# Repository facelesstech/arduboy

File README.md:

# arduboy
arduboy with flashcart

Blog post - https://facelesstech.wordpress.com/2019/10/12/arduboy-with-removable-flash-cart/
Youtube - https://youtu.be/qZQMl9mM28Q

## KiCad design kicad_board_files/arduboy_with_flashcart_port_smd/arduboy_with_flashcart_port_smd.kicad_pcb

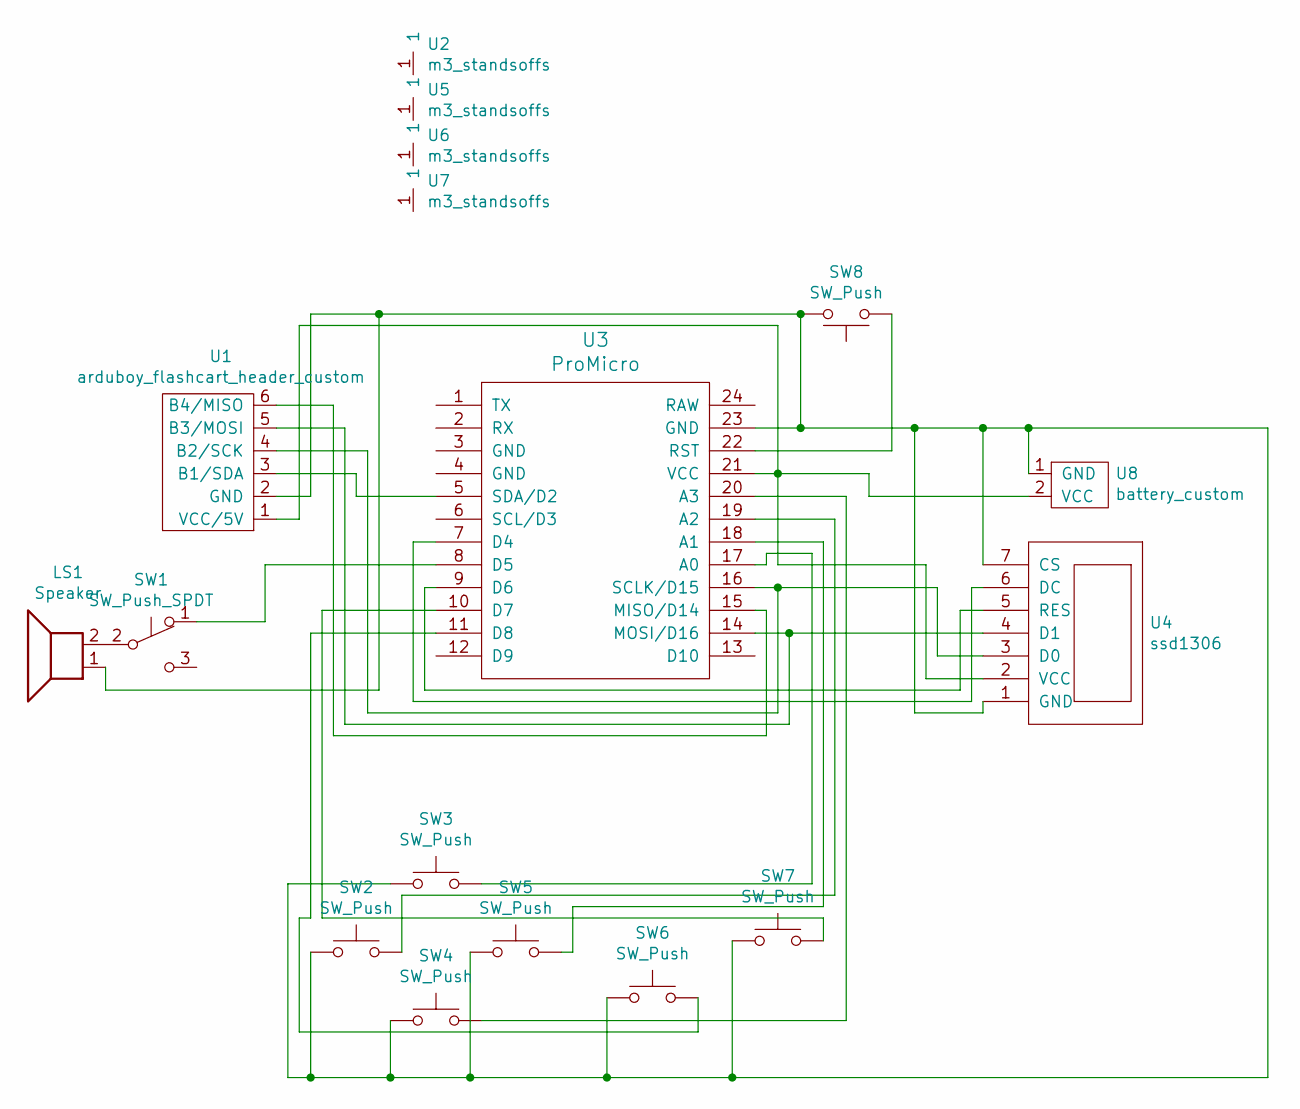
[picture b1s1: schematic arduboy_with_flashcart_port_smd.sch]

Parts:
LS1: Speaker; piezo_smd
SW1: SW_Push_SPDT; tiny_smd_slide_switch_custom
SW2, SW3, SW4, SW5, SW6, SW7: SW_Push; smd_soft_custom
SW8: SW_Push; SMD_2pin_button_custom
U1: arduboy_flashcart_header_custom; arduboy_flashcart_port_flashcart_outline
U2, U5, U6, U7: m3_standsoffs; m3_hole_custom
U3: ProMicro; ProMicro_smd_pads
U4: ssd1306; SSD1306_oled_screen
U8: battery_custom; battery_connector_custom

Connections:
unnamed: LS1.1, SW2.1, SW3.1, SW4.1, SW5.1, SW6.1, SW7.1, SW8.2, U1.2 (GND), U3.23 (GND), U4.1 (GND), U4.7 (CS), U8.1 (GND)
unnamed: LS1.2, SW1.2 (B)
unnamed: SW1.1 (A), U3.8 (D5)
unnamed: SW2.2, U3.19 (A2)
unnamed: SW3.2, U3.17 (A0)
unnamed: SW4.2, U3.20 (A3)
unnamed: SW5.2, U3.18 (A1)
unnamed: SW6.2, U3.11 (D8)
unnamed: SW7.2, U3.10 (D7)
unnamed: SW8.1, U3.22 (RST)
unnamed: U1.1 (VCC/5V), U3.21 (VCC), U4.2 (VCC), U8.2 (VCC)
unnamed: U1.3 (B1/SDA), U3.5 (SDA/D2)
unnamed: U1.4 (B2/SCK), U3.16 (SCLK/D15), U4.3 (D0)
unnamed: U1.5 (B3/MOSI), U3.14 (MOSI/D16), U4.4 (D1)
unnamed: U1.6 (B4/MISO), U3.15 (MISO/D14)
unnamed: U3.7 (D4), U4.6 (DC)
unnamed: U3.9 (D6), U4.5 (RES)

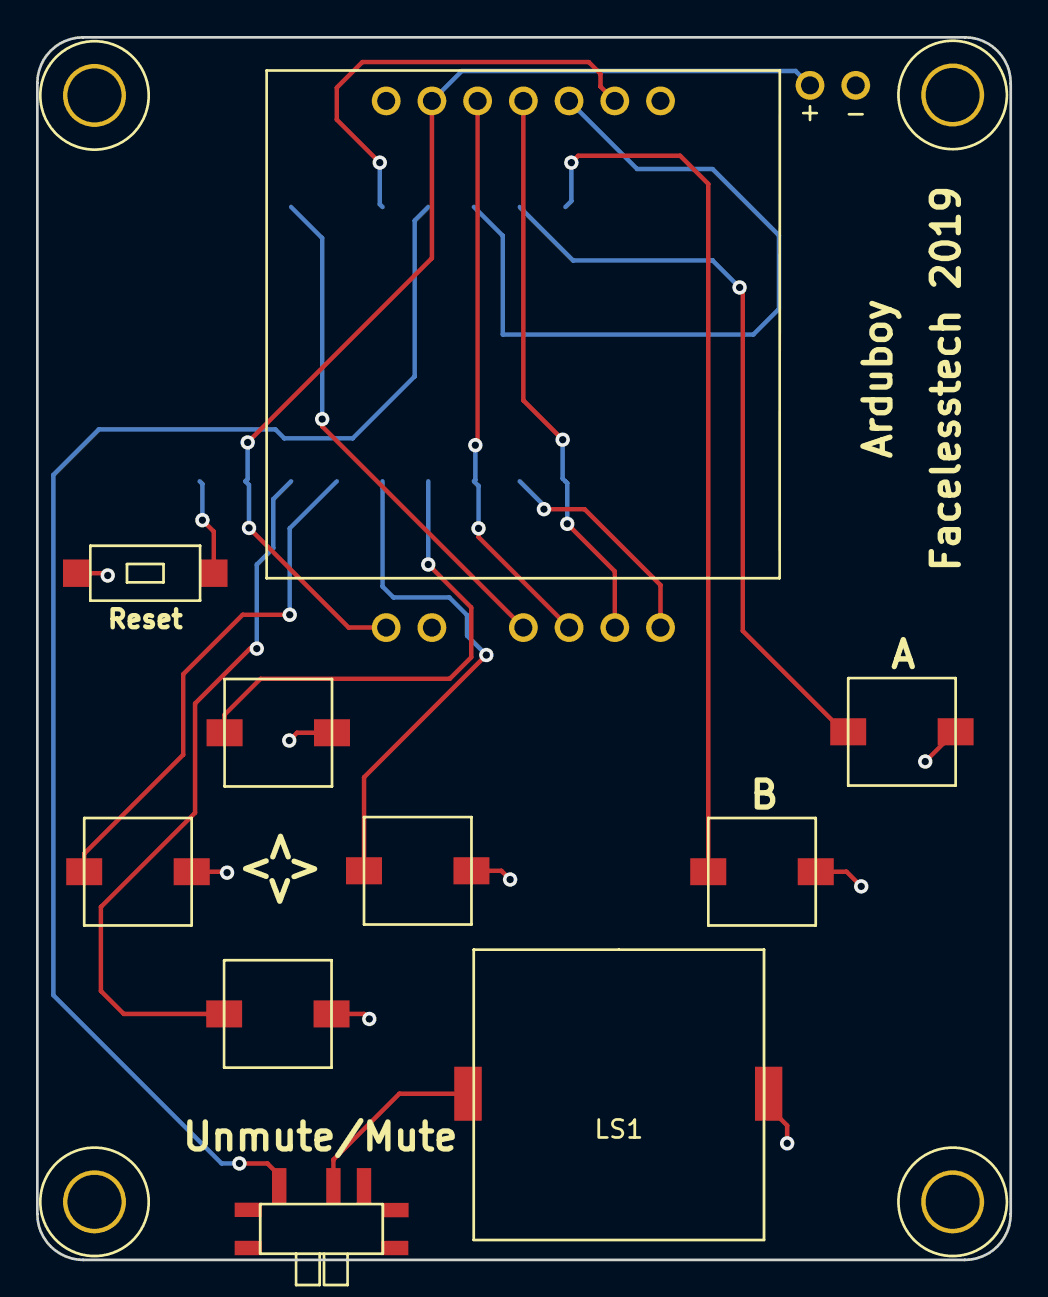
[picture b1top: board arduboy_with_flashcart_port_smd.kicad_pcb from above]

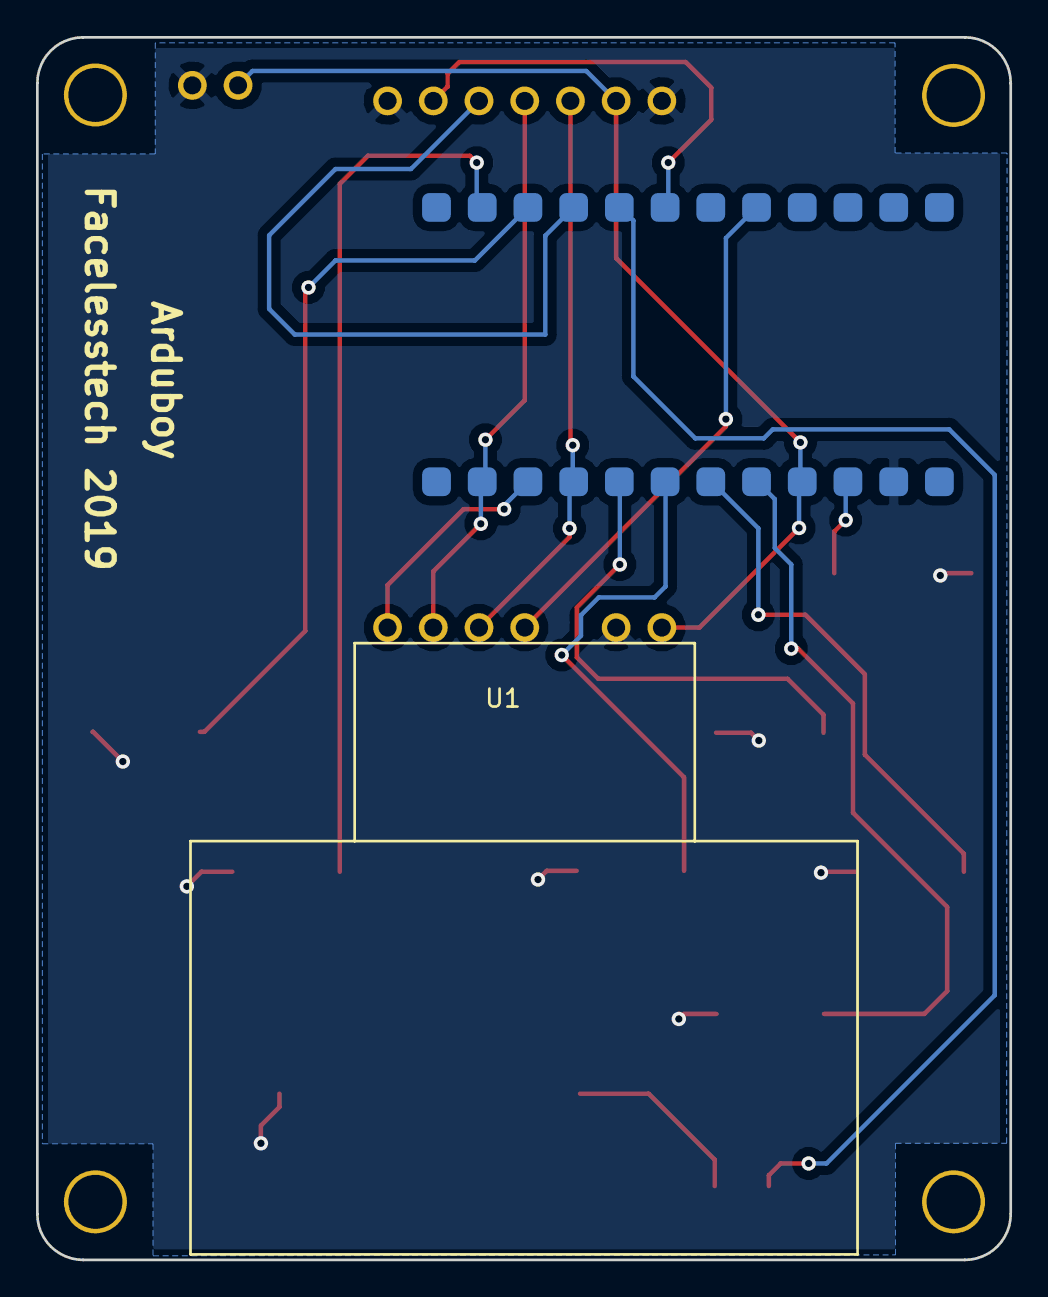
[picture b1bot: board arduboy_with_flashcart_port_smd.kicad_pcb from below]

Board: 2 copper layers, 54.1 x 67.9 mm, 17 parts (2 on the bottom side), 17 nets.

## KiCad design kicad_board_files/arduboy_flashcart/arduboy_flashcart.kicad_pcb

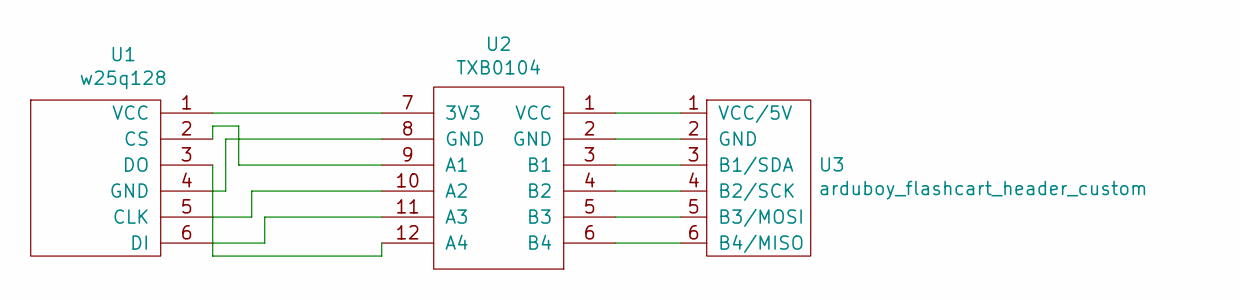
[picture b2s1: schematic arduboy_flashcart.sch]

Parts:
U1: w25q128; W25Q128
U2: TXB0104
U3: arduboy_flashcart_header_custom; arduboy_flashcart_port_smd

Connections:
unnamed: U1.1 (VCC), U2.7 (3V3)
unnamed: U1.2 (CS), U2.9 (A1)
unnamed: U1.3 (DO), U2.12 (A4)
unnamed: U1.4 (GND), U2.8 (GND)
unnamed: U1.5 (CLK), U2.10 (A2)
unnamed: U1.6 (DI), U2.11 (A3)
unnamed: U2.1 (VCC), U3.1 (VCC/5V)
unnamed: U2.2 (GND), U3.2 (GND)
unnamed: U2.3 (B1), U3.3 (B1/SDA)
unnamed: U2.4 (B2), U3.4 (B2/SCK)
unnamed: U2.5 (B3), U3.5 (B3/MOSI)
unnamed: U2.6 (B4), U3.6 (B4/MISO)

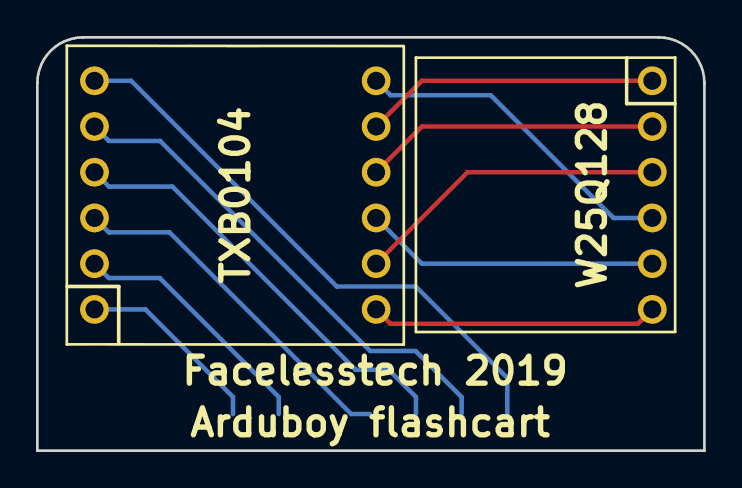
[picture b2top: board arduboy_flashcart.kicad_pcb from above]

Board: 2 copper layers, 37.1 x 23.0 mm, 3 parts (1 on the bottom side), 12 nets.

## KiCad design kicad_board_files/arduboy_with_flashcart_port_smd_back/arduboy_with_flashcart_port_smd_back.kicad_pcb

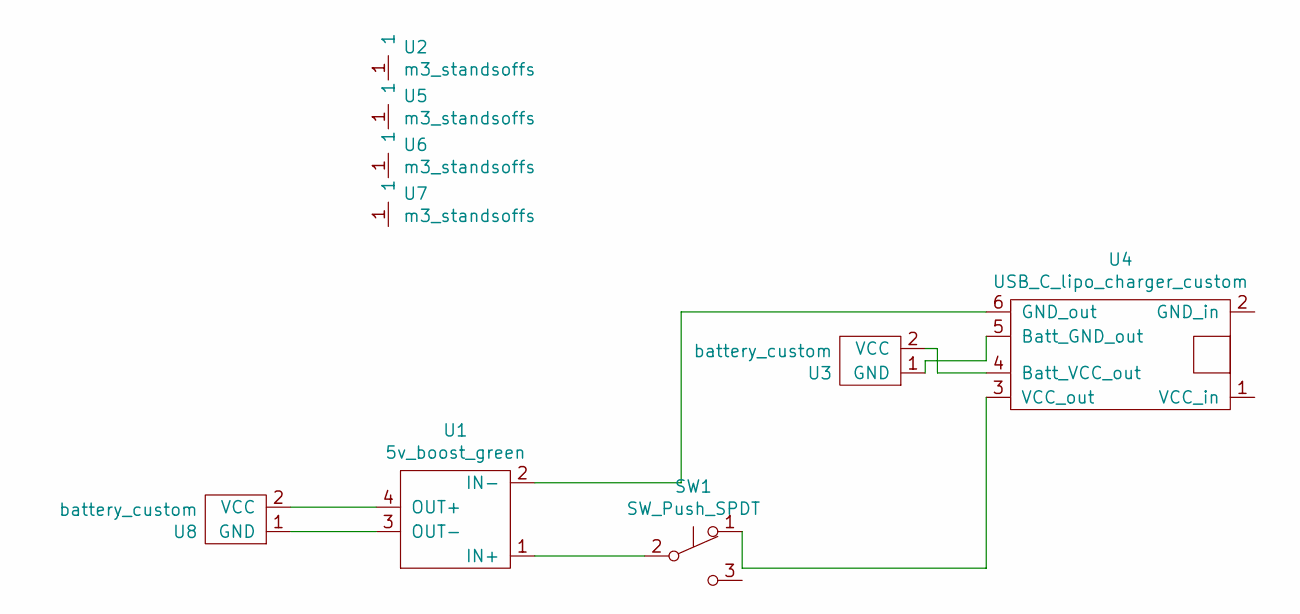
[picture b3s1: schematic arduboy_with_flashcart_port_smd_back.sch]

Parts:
SW1: SW_Push_SPDT; tiny_smd_slide_switch_custom
U1: 5v_boost_green; usb_5v_boost_green
U2, U5, U6, U7: m3_standsoffs; m3_hole_custom
U3: battery_custom; jst_2pin_right_angle
U4: USB_C_lipo_charger_custom
U8: battery_custom; battery_connector_custom

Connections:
unnamed: SW1.1 (A), U4.3 (VCC_out)
unnamed: SW1.2 (B), U1.1 (IN+)
unnamed: U1.2 (IN-), U4.6 (GND_out)
unnamed: U1.3 (OUT-), U8.1 (GND)
unnamed: U1.4 (OUT+), U8.2 (VCC)
unnamed: U3.1 (GND), U4.5 (Batt_GND_out)
unnamed: U3.2 (VCC), U4.4 (Batt_VCC_out)

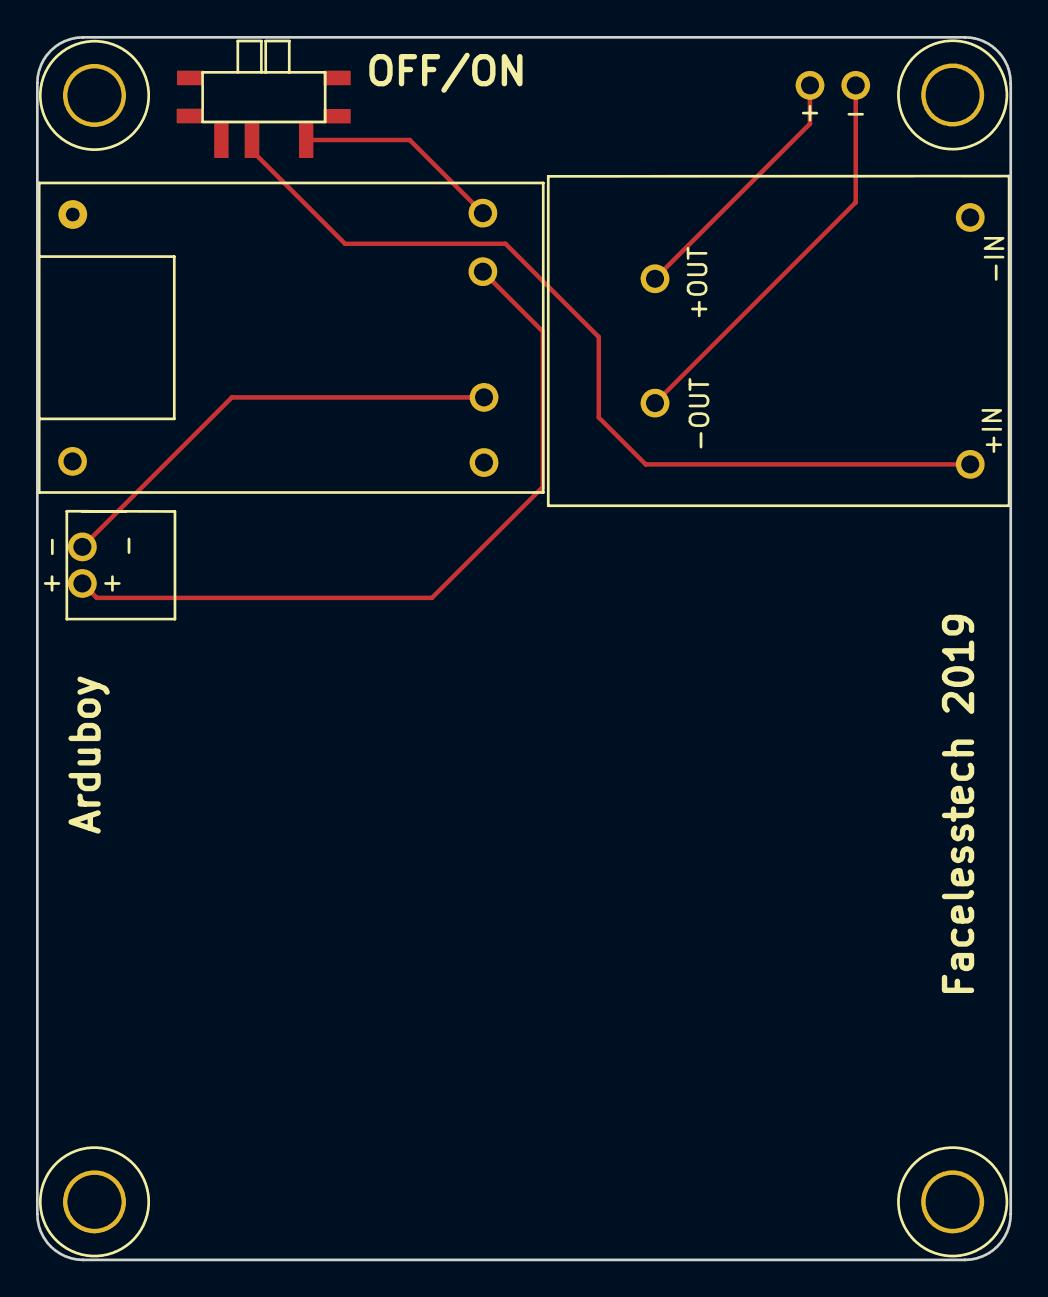
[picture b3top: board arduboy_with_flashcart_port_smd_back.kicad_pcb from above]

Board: 2 copper layers, 54.1 x 67.9 mm, 9 parts (0 on the bottom side), 7 nets.

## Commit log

2019-10-12 board files
2020-02-27 added links to readme
